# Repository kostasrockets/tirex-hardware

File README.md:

# tirex-hardware
hardware for tirex

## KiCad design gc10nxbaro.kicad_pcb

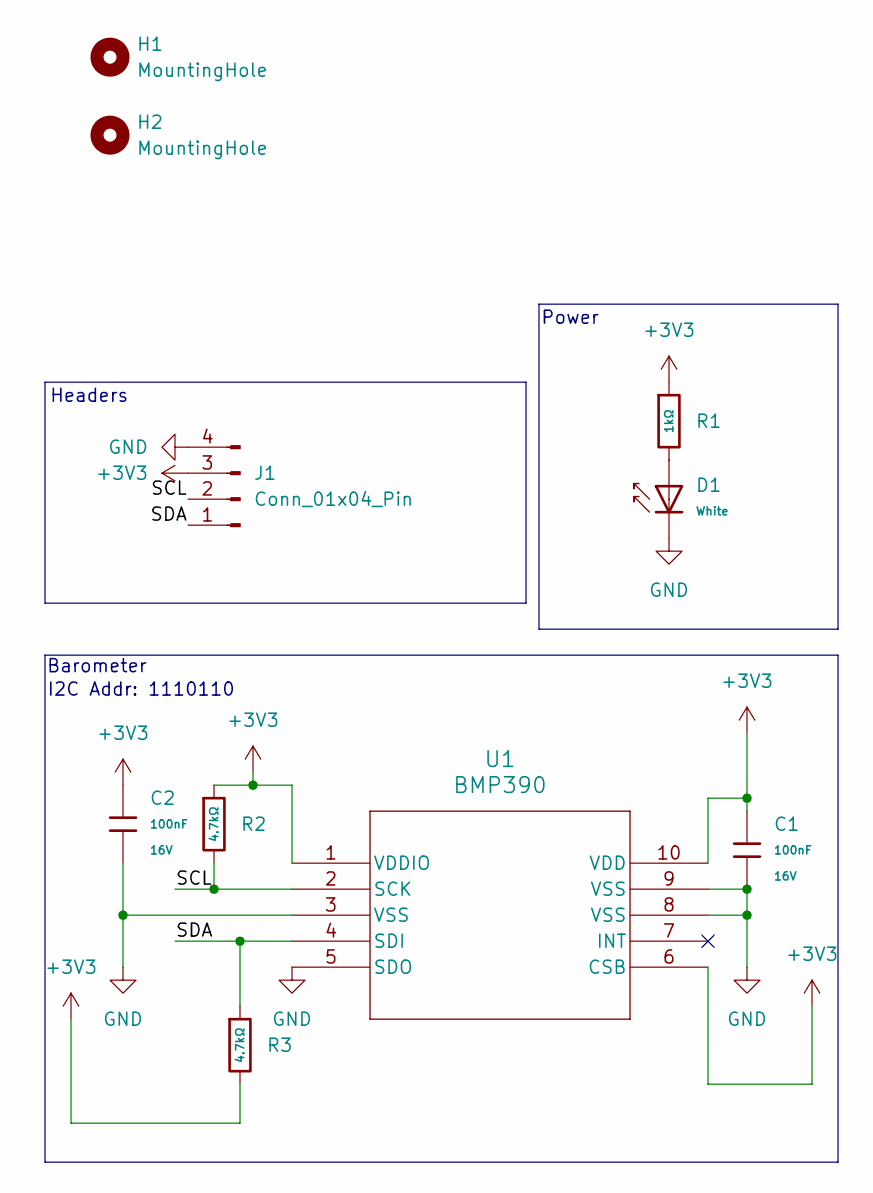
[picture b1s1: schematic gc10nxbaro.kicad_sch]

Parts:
C1, C2: 100nF; C_0402; Voltage Rated 16V; Tolerance ±10%; Part CL05B104KO5NNNC; LCSC C1525
D1: White; D_0805; Part KT-0805W; LCSC C34499
H1, H2: MountingHole; MountingHole_2.2mm_M2
J1: Conn_01x04_Pin; PinHeader_1x04_P2.54mm_Vertical
R1: 1kΩ; R_0402; Overload Voltage (Max) 50V; Tolerance ±1%; Part 0402WGF1001TCE; LCSC C11702
R2, R3: 4.7kΩ; R_0402; Overload Voltage (Max) 50V; Tolerance ±1%; Part 0402WGF4701TCE; LCSC C25900
U1: BMP390; 10LGA_2X2X0p75_BOS

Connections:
+3V3: C1.1, C2.1, J1.3, R1.1, R2.1, R3.2, U1.1 (VDDIO), U1.6 (CSB), U1.10 (VDD)
/SCL: J1.2, R2.2, U1.2 (SCK)
/SDA: J1.1, R3.1, U1.4 (SDI)
GND: C1.2, C2.2, D1.1, J1.4, U1.3 (VSS), U1.5 (SDO), U1.8 (VSS), U1.9 (VSS)
unnamed: D1.2, R1.2

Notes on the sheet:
Barometer
Power
I2C Addr: 1110110
Headers

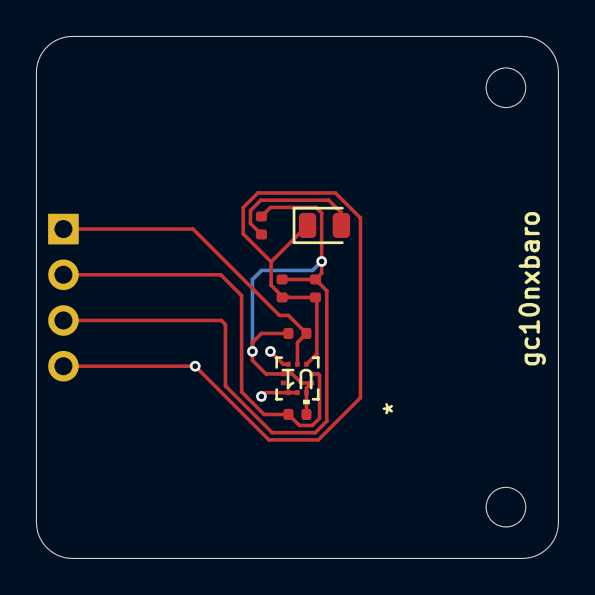
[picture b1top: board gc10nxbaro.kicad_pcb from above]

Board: 2 copper layers, 29.0 x 29.0 mm, 10 parts (1 on the bottom side), 5 nets.
